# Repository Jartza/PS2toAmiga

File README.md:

# PS2toAmiga
Simple ATTiny85 based PS/2 to Amiga keyboard protocol converter that fits inside the keyboard.

The project was born as an idea to get small and color-matching keyboard to my old
Commodore Amiga CD32 console, in order to make it more Amiga-like, in use with
TerribleFire 330. I found few projects around The Net which did the same thing but some
of them used old and almost unobtainable ICs with closed firmware and some didn't work
that well.

Many projects used just way too big chip for the job, which I felt was a waste of precious
silicon, as you only need 2 input and 2 output pins for the job - ATTiny85 was chosen as
it's one of my favorite "all 'round" chip for simple tasks.

I wanted the adapter to sit inside the keyboard and use the CD32 AUX-connector (PS/2 style
mini-DIN) as-is for cable.

Of course the keyboard protocol is the same in all Amigas, the pinouts just differ, so this
project can be used to create replacement keyboard for the lost one to your bigger Amigas
as well (like Amiga 2000, 3000 & 4000 etc.)

## How it works

PS/2 keyboard protocol in it's basic level isn't that hard, it is bidirectional synchronous
serial port with clock (CLK) and data (DATA) lines, communicating with PS/2 keyboard using
microcontroller has been done multiple times already - which is why I chose to use
PS2KeyAdvanced library for Arduino to handle that task - I didn't want to re-invent the wheel,
and I had already used PS2KeyAdvanced in earlier projects as well. It also has nice support
for Caps Lock, Num Lock etc.

The keycodes read from PS/2 keyboard using PS2KeyAdvanced are then [translated to the respective
Amiga keycode](convert_table.h) and sent to wire, using
[Amiga keyboard protocol](http://amigadev.elowar.com/read/ADCD_2.1/Hardware_Manual_guide/node0172.html).

The converter-code also keeps track of user pressing CTRL-Amiga-Amiga simultaneously and
implements [resetting the Amiga](http://amigadev.elowar.com/read/ADCD_2.1/Hardware_Manual_guide/node0179.html)
when those keys are pressed. 

There are two different layouts, selectable with Scroll Lock (when Scroll Lock LED is on, second
layout is in use). In first layout, Windows/Menu-keys are mapped to respective
Amiga-keys on both sides of the space bar, Alt-keys are mapped to respective Amiga versions. 
On second layout, Left CTRL is mapped to CTRL, Right CTRL to ALT, ALT to Right Amiga-key. Also
on second layout, F11 and F12 are mapped to Left and Right Amiga-keys.

Mofifying the keyboard mapping should be pretty straight forward, in the table the comment after
keycode denotes the respective key on PS/2 keyboard and the Amiga keycode can be checked from
[this image](images/amigakeys.png). Do not remove values from the table, and do not change the 
order of the items! Only change the HEX Amiga keycode, before the comment.

Code itself is "quick'n'dirty" -style but should be pretty much commented out so you can modify
the internals of it to your own needs - if you have any.

## Installing

See [PS2KeyAdvanced](https://github.com/techpaul/PS2KeyAdvanced) project for install instructions,
for some reason the version 1.0.9 failed to install into my pretty recent Arduino install, but
version 1.0.8 worked as well.

For ATTiny85 support I used [ATTinyCore](https://github.com/SpenceKonde/ATTinyCore), again check
their respective site for install instructions to your Arduino IDE.

After installing ATTinyCore and PS2KeyAdvanced, load the project into your Arduino IDE and 
select following settings:

- **Board:** ATtiny24/45/85 (No bootloader)
- **Chip:** ATtiny85
- **Clock Source**: 16 MHz (PLL)
- **TImer 1 Clock:** CPU frequency
- **LTO:** Enabled
- **millis():** Enabled

#### Steps to install to ATTiny85:

Use whatever ISP programmer you have. I used cheap USBASP programmer with 10 -> 6 pin adapter cable,
having header pins in ISP connector and then pushing the connector into ISP holes (no header soldered)
and keeping them tilted in an angle during programming.

1. Tools -> Burn bootloader (actually only sets fuses, and enables 16MHz PLL clock)
2. Sketch -> Verify/Compile
3. Upload using programmer

You should be done now, if not, verify your programmer connections. I also have had issue sometimes
programming the new parts, which are set to 1MHz default in factory - you might need to change your
Arduino settings to slow down the programmer for Fuse burning.

## Connecting the adapter

Wiring the keyboard to your Amiga and PCB should be pretty obvious in the following diagram:

If that is not clear enough, the underside of the PCB has each pin function named.

Several Amigas have different pinouts, Google is your friend here.

**Word of warning:** if you think of re-using the PS/2 keyboard cable, be warned that most of
the keyboards only have 4-wire cable in them and probably the necessary pins are not connected
at all (at least if the Amiga you want to connect to has mini-DIN style keyboard connector).
I solved this issue by ordering PS/2 extension cable and just cutting off the female plug and
then using multimeter to solve cable colors to pins connection. Those extension cables usually
have all the 6 wires connected and it's much easier to use them than to solder those pesky
mini-DIN connectors.

## PCB

PCB files are in [pcb](pcb/) -folder, also including [gerbers](pcb/gerbers/), if you just want
to order the PCB. Schematics are respectively in [schematics](schematics/) -folder.
Bill of Materials, [BOM](schematics/BOM.txt) is also provided.

PCB and Schematics were designed using Eagle 9.6.1 free edition.

### Top side:

### Bottom side:

### Other

Please report any [issues](https://github.com/Jartza/PS2toAmiga/issues) you find with the code!

You can also participate in [discussions](https://github.com/Jartza/PS2toAmiga/discussions) without opening an issue. All enhancement ideas, questions etc. are welcome.

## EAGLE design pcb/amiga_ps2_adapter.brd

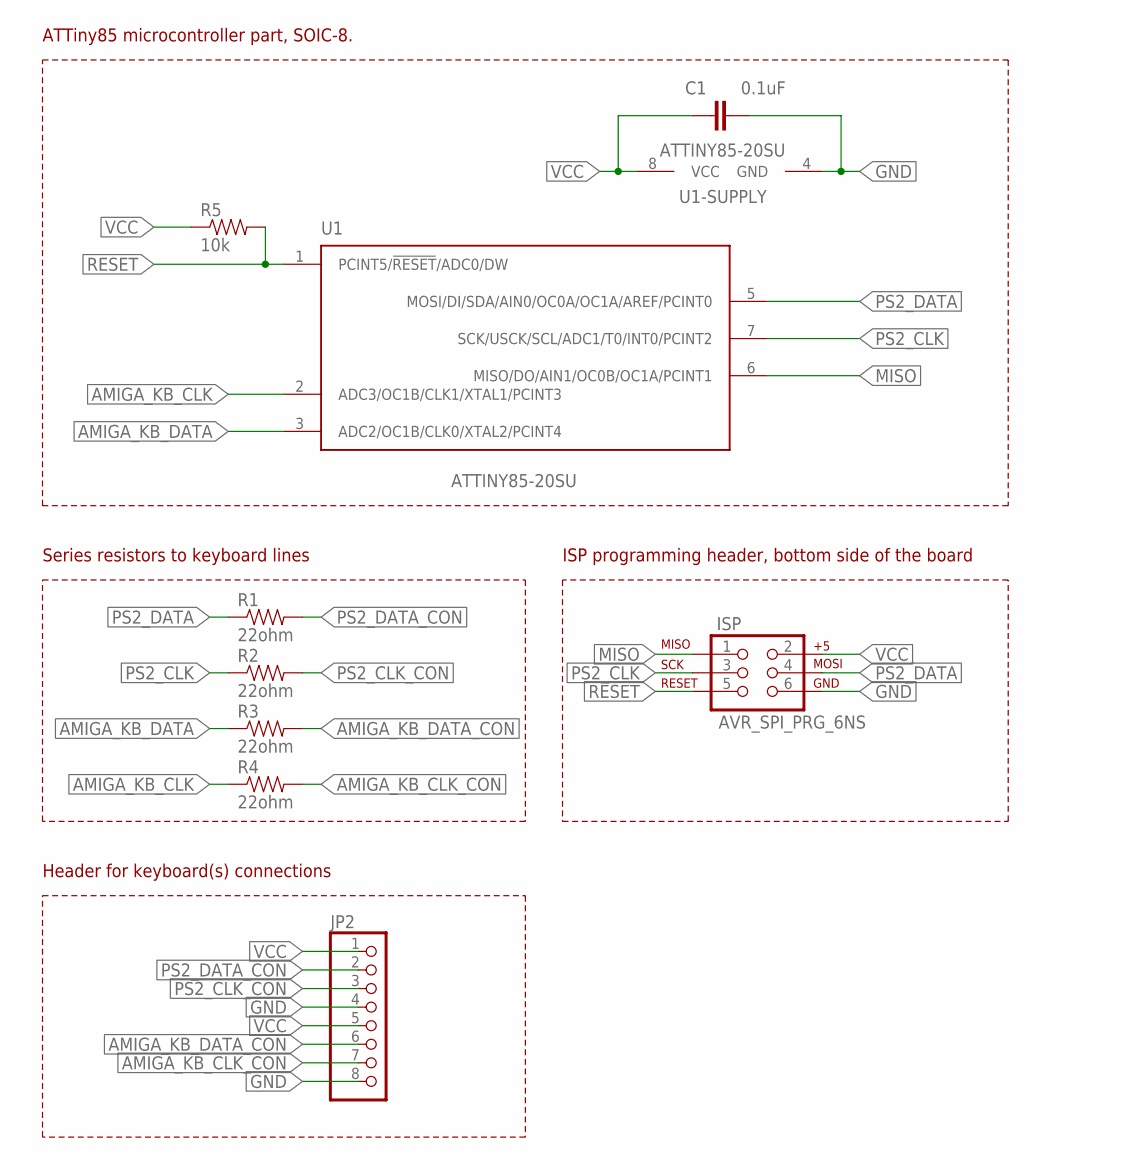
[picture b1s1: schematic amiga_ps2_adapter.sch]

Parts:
C1: 0.1uF; 0603-CAP
ISP: AVR_SPI_PRG_6NS; 2X3-NS
JP2: HEADER-1X8ROUND; 1X08_ROUND
R1, R2, R3, R4: 22ohm; 0603-RES
R5: 10k; 0603-RES
U1: ATTINY85-20SU; SOIC-8

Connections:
AMIGA_KB_CLK: R4.1, U1.2 (ADC3/OC1B/CLK1/XTAL1/PCINT3)
AMIGA_KB_CLK_CON: JP2.7, R4.2
AMIGA_KB_DATA: R3.1, U1.3 (ADC2/OC1B/CLK0/XTAL2/PCINT4)
AMIGA_KB_DATA_CON: JP2.6, R3.2
GND: C1.2, ISP.6, JP2.4, JP2.8, U1.4 (GND)
MISO: ISP.1, U1.6 (MISO/DO/AIN1/OC0B/OC1A/PCINT1)
PS2_CLK: ISP.3, R2.1, U1.7 (SCK/USCK/SCL/ADC1/T0/INT0/PCINT2)
PS2_CLK_CON: JP2.3, R2.2
PS2_DATA: ISP.4, R1.1, U1.5 (MOSI/DI/SDA/AIN0/OC0A/OC1A/AREF/PCINT0)
PS2_DATA_CON: JP2.2, R1.2
RESET: ISP.5, R5.2, U1.1 (PCINT5/!RESET!/ADC0/DW)
VCC: C1.1, ISP.2, JP2.1, JP2.5, R5.1, U1.8 (VCC)

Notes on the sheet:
ATTiny85 microcontroller part, SOIC-8.
ISP programming header, bottom side of the board
Series resistors to keyboard lines
Header for keyboard(s) connections

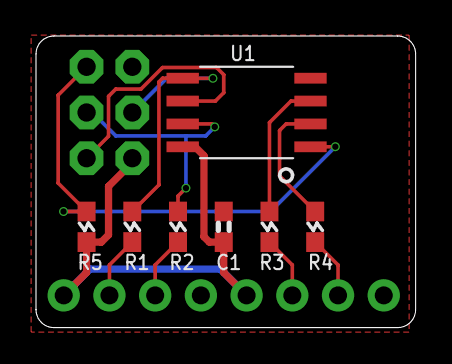
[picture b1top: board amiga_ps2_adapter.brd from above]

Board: 2 copper layers, 21.1 x 16.2 mm, 9 parts (1 on the bottom side), 12 nets.

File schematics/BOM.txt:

Bill of materials for PS2 to Amiga keyboard converter using ATTiny85
====================================================================


Designator                  Part                        Footprint
----------                  ----                        ---------
 U1                         ATTINY85-20SUR              SOIC-8
 R1,R2,R3,R4                Resistor 22-47 ohms         0603
 R5                         Resistor 4.7-10 kohms       0603
 ISP                        2x3 pinheader (NP)          2.54mm pitch
 J2                         1x8 pinheader (NP)          2.54mm pitch


 NOTE:

 (NP) parts = Not Populated.

 ISP header is only used for programming (from the bottom side of the board!)
 and probably doesn't need to be populated, just press programming cable
 with header pin inserts into the connector holes and tilt a bit during
 ATTiny85 ISP programming.

 J2 is for keyboard connection but as probably this will sit inside the
 keyboard (or in the middle of cable inside stress relief box) you will
 most probably solder the keyboard wires directly to the header.

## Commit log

2022-01-28 Initial release
2022-01-28 Add PCB and Schematics
2022-01-28 Add BOM
2022-01-28 Update BOM
2022-01-28 Add connection image
2022-01-28 Add images
2022-01-28 Update diagram
2022-01-29 Map: F11=Left Amiga, F12=Right Amiga#
2022-01-29 Change README
2022-01-29 Fix Arduino compile
2022-01-29 Rename include folder
2022-02-01 Try to make tabs show in Arduino IDE
2022-02-16 Make two convert tables
2022-02-16 Fix reset
2022-02-16 Fix scroll lock state
2022-02-16 Add image
2022-03-01 Increase delay a slight bit, helps with some games

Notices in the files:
pcb/amiga_ps2_adapter.brd:
(C) 2022
parts and their libraries:
SparkFun-Capacitors: Licensing: Creative Commons ShareAlike 4.0 International - https://creativecommons.org/licenses/by-sa/4.0
microbuilder: This work is placed in the public domain, and may be freely used for commercial and non-commercial work with the following conditions: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
